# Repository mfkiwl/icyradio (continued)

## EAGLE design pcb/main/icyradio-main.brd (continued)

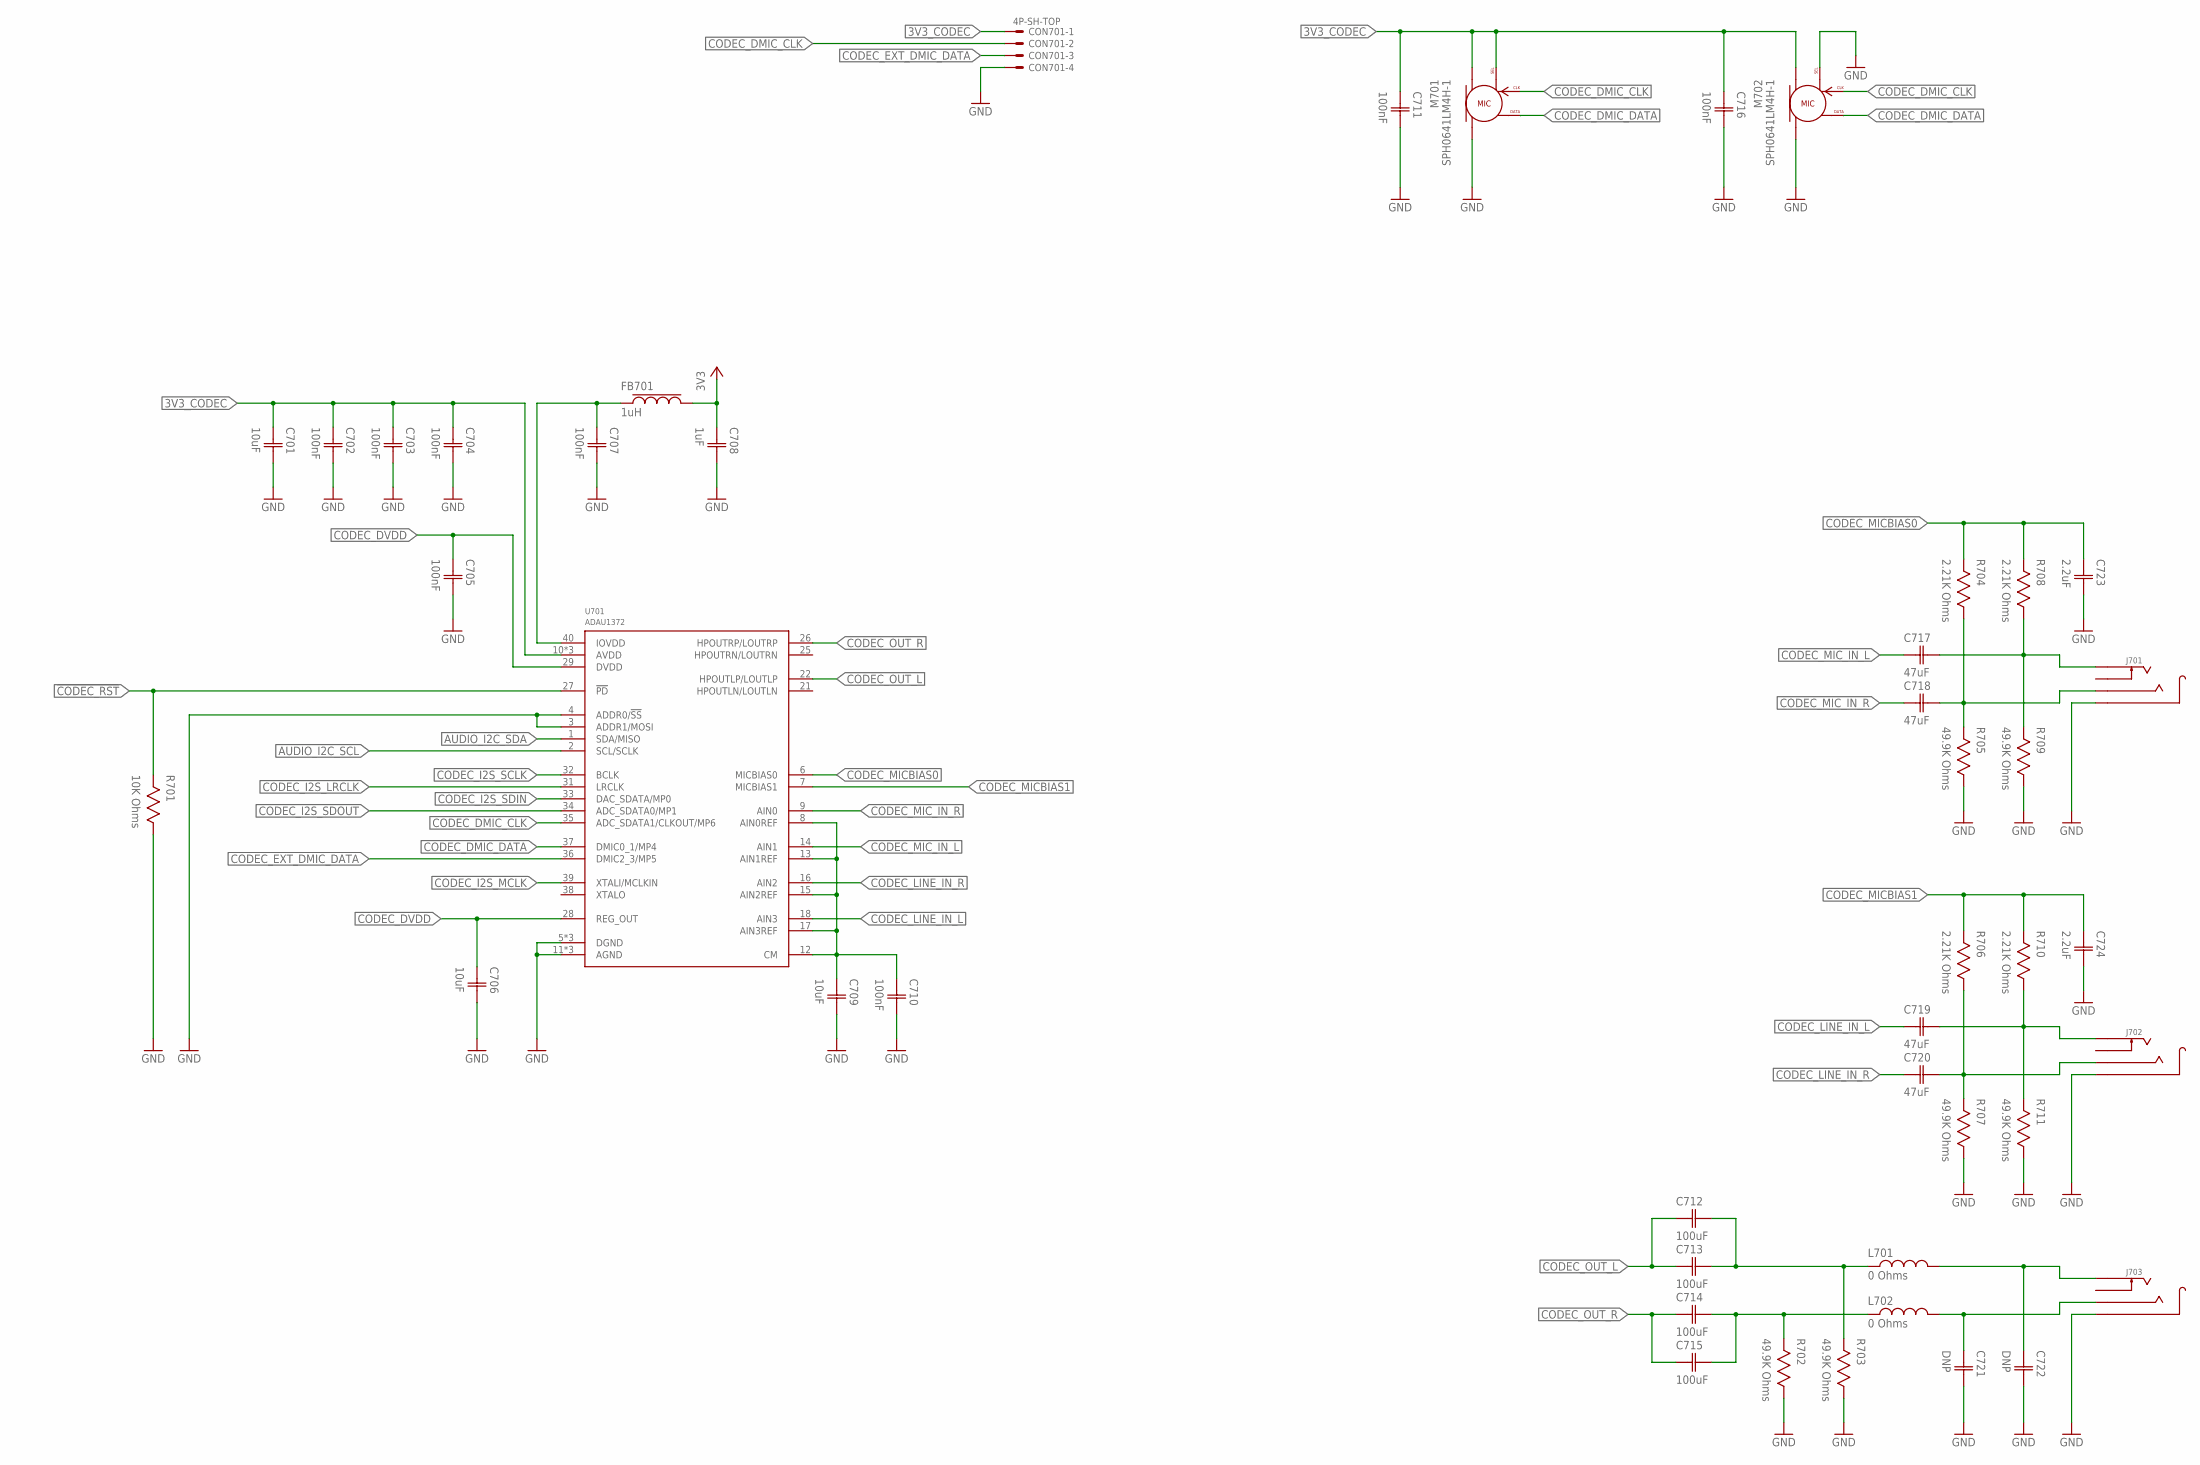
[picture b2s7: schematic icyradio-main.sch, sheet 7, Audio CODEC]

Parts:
C701, C706, C709: 10uF; CAP0402
C702, C703, C704, C705, C707, C710, C711, C716: 100nF; CAP0402
C708: 1uF; CAP0402
C712, C713, C714, C715: 100uF; CAP0805
C717, C718, C719, C720: 47uF; CAP0603
C721, C722: DNP; CAP0402
C723, C724: 2.2uF; CAP0402
CON701: 4P-SH-TOP; SH-04-TOP
FB701: 1uH; IND0603
J701, J702, J703: TRSJACK; 3.5TRSJACK
L701, L702: 0 Ohms; IND0603
M701, M702: SPH0641LM4H-1
R701: 10K Ohms; RES0402
R702, R703, R705, R707, R709, R711: 49.9K Ohms; RES0402
R704, R706, R708, R710: 2.21K Ohms; RES0402
U701: ADAU1372; QFN40

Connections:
3V3: C708.1 (C1), FB701.2; also elsewhere on the board
3V3_CODEC: C701.1 (C1), C702.1 (C1), C703.1 (C1), C704.1 (C1), C711.1 (C1), C716.1 (C1), CON701.1, M701.2 (SEL), M701.5 (VCC), M702.5 (VCC), U701.10 (AVDD), U701.19 (AVDD), U701.24 (AVDD); also elsewhere on the board
3V3_CODEC_DIG: C707.1 (C1), FB701.1, U701.40 (IOVDD)
!CODEC_RST: R701.2, U701.27 (!PD); also elsewhere on the board
AUDIO_I2C_SCL: U701.2 (SCL/SCLK); also elsewhere on the board
AUDIO_I2C_SDA: U701.1 (SDA/MISO); also elsewhere on the board
CODEC_CM: C709.1 (C1), C710.1 (C1), U701.8 (AIN0REF), U701.12 (CM), U701.13 (AIN1REF), U701.15 (AIN2REF), U701.17 (AIN3REF)
CODEC_DMIC_CLK: CON701.2, M701.4 (CLK), M702.4 (CLK), U701.35 (ADC_SDATA1/CLKOUT/MP6)
CODEC_DMIC_DATA: M701.1 (DAT), M702.1 (DAT), U701.37 (DMIC0_1/MP4)
CODEC_DVDD: C705.1 (C1), C706.1 (C1), U701.28 (REG_OUT), U701.29 (DVDD)
CODEC_EXT_DMIC_DATA: CON701.3, U701.36 (DMIC2_3/MP5)
CODEC_I2S_LRCLK: U701.31 (LRCLK); also elsewhere on the board
CODEC_I2S_MCLK: U701.39 (XTALI/MCLKIN); also elsewhere on the board
CODEC_I2S_SCLK: U701.32 (BCLK); also elsewhere on the board
CODEC_I2S_SDIN: U701.33 (DAC_SDATA/MP0); also elsewhere on the board
CODEC_I2S_SDOUT: U701.34 (ADC_SDATA0/MP1); also elsewhere on the board
CODEC_LINE_IN_L: C719.1 (C1), U701.18 (AIN3)
CODEC_LINE_IN_R: C720.1 (C1), U701.16 (AIN2)
CODEC_MICBIAS0: C723.1 (C1), R704.2, R708.2, U701.6 (MICBIAS0)
CODEC_MICBIAS1: C724.1 (C1), R706.2, R710.2, U701.7 (MICBIAS1)
CODEC_MIC_IN_L: C717.1 (C1), U701.14 (AIN1)
CODEC_MIC_IN_R: C718.1 (C1), U701.9 (AIN0)
CODEC_OUT_L: C712.1 (C1), C713.1 (C1), U701.22 (HPOUTLP/LOUTLP)
CODEC_OUT_R: C714.1 (C1), C715.1 (C1), U701.26 (HPOUTRP/LOUTRP)
GND: C701.2 (C2), C702.2 (C2), C703.2 (C2), C704.2 (C2), C705.2 (C2), C706.2 (C2), C707.2 (C2), C708.2 (C2), C709.2 (C2), C710.2 (C2), C711.2 (C2), C716.2 (C2), C721.2 (C2), C722.2 (C2), C723.2 (C2), C724.2 (C2), CON701.4, J701.1 (S), J702.1 (S), J703.1 (S), M701.3 (GND), M702.2 (SEL), M702.3 (GND), R701.1, R702.1, R703.1, R705.1, R707.1, R709.1, R711.1, U701.3 (ADDR1/MOSI), U701.4 (ADDR0/!SS), U701.5 (DGND), U701.11 (AGND), U701.20 (AGND), U701.23 (AGND), U701.30 (DGND), U701.41 (DGND); also elsewhere on the board
unnamed: C720.2 (C2), J702.3 (R), R706.1, R707.2
unnamed: C719.2 (C2), J702.2 (T), R710.1, R711.2
unnamed: C718.2 (C2), J701.3 (R), R704.1, R705.2
unnamed: C717.2 (C2), J701.2 (T), R708.1, R709.2
unnamed: C714.2 (C2), C715.2 (C2), L702.1, R702.2
unnamed: C712.2 (C2), C713.2 (C2), L701.1, R703.2
unnamed: C721.1 (C1), J703.3 (R), L702.2
unnamed: C722.1 (C1), J703.2 (T), L701.2

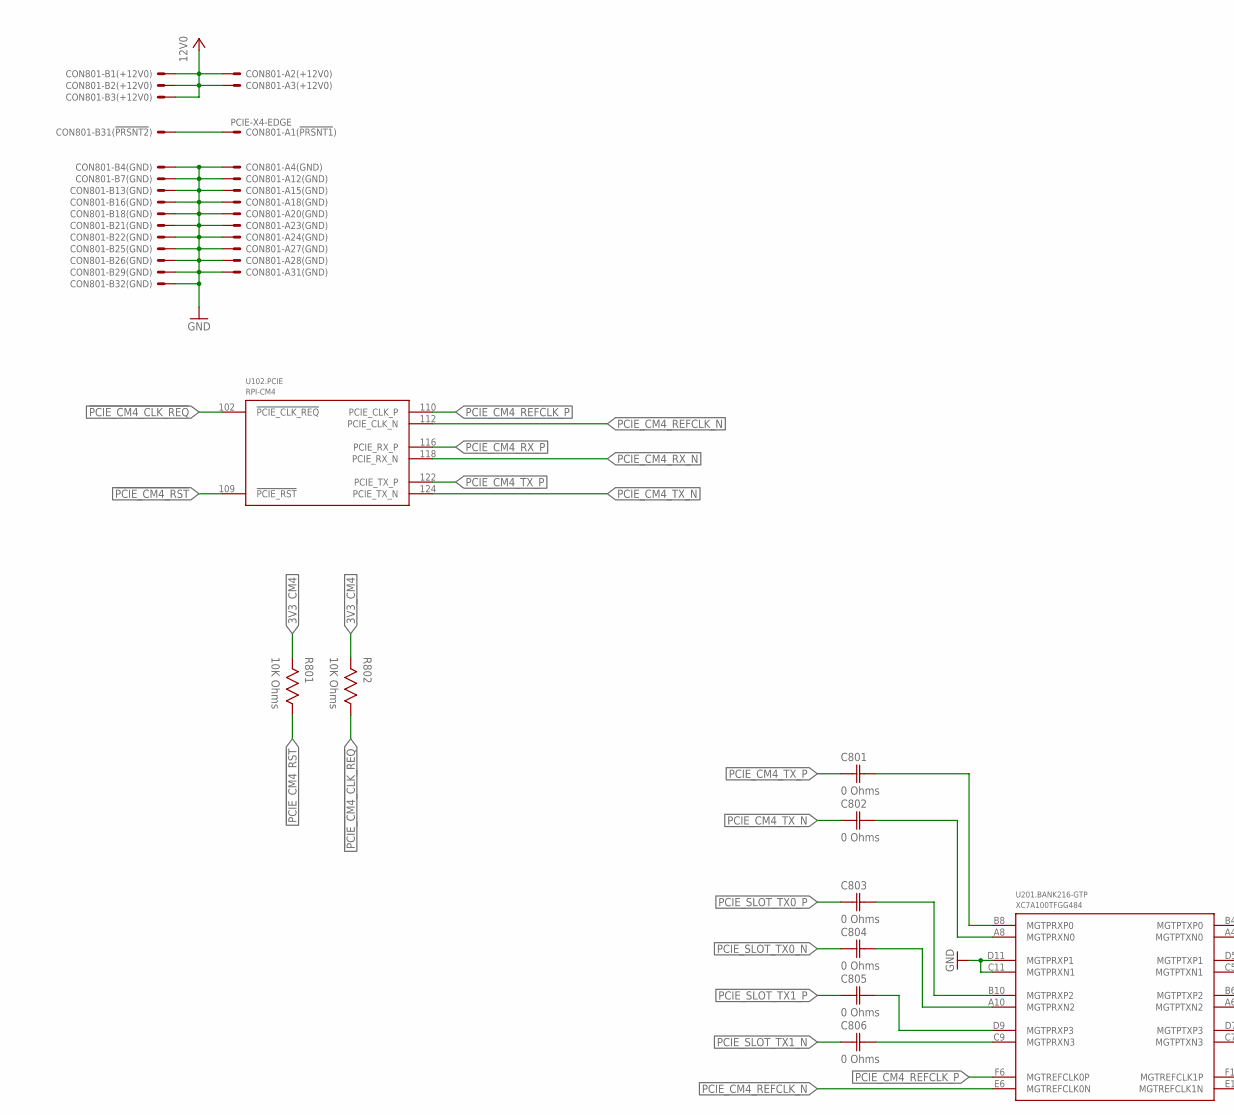
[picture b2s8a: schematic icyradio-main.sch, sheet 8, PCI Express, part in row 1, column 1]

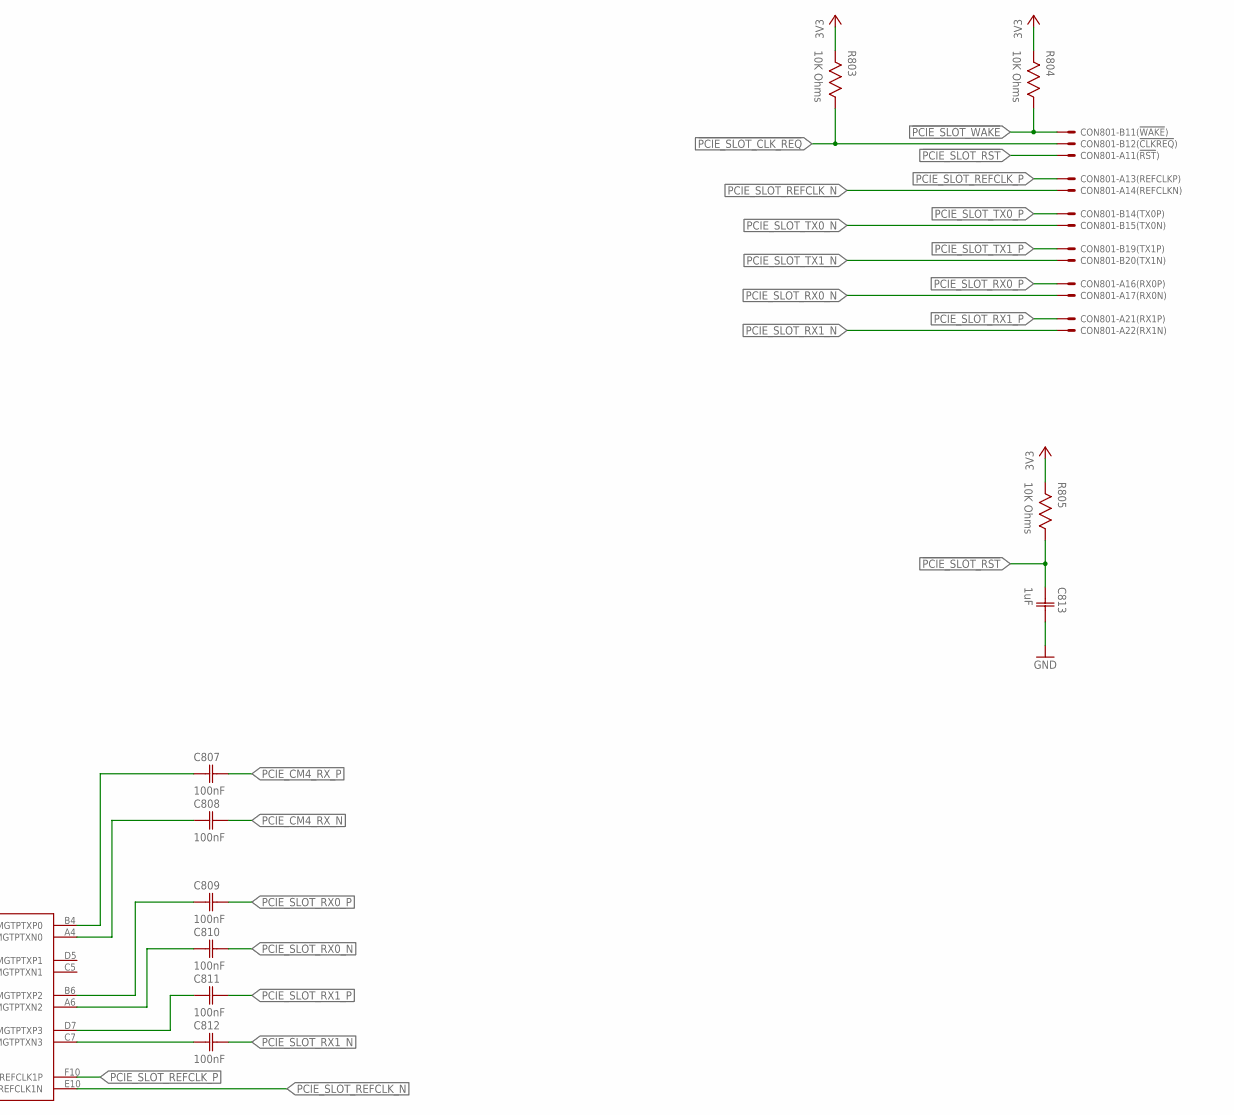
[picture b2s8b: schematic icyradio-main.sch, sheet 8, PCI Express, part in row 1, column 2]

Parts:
C801, C802, C803, C804, C805, C806: 0 Ohms; CAP0402
C807, C808, C809, C810, C811, C812: 100nF; CAP0402
C813: 1uF; CAP0402
CON801: PCIE-X4-EDGE
R801, R802, R803, R804, R805: 10K Ohms; RES0402
U102: RPI-CM4
U201: XC7A100TFGG484; FGG484

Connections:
3V3: R803.2, R804.2, R805.2; also elsewhere on the board
3V3_CM4: R801.2, R802.2; also elsewhere on the board
12V0: CON801.A2, CON801.A3, CON801.B1, CON801.B2, CON801.B3; also elsewhere on the board
!PCIE_CM4_CLK_REQ: R802.1, U102.102 (!PCIE_CLK_REQ); also elsewhere on the board
!PCIE_CM4_RST: R801.1, U102.109 (!PCIE_RST); also elsewhere on the board
!PCIE_SLOT_CLK_REQ: CON801.B12, R803.1; also elsewhere on the board
!PCIE_SLOT_PRSNT: CON801.A1, CON801.B31
!PCIE_SLOT_RST: C813.1 (C1), CON801.A11, R805.1; also elsewhere on the board
!PCIE_SLOT_WAKE: CON801.B11, R804.1; also elsewhere on the board
GND: C813.2 (C2), CON801.A4, CON801.A12, CON801.A15, CON801.A18, CON801.A20, CON801.A23, CON801.A24, CON801.A27, CON801.A28, CON801.A31, CON801.B4, CON801.B7, CON801.B13, CON801.B16, CON801.B18, CON801.B21, CON801.B22, CON801.B25, CON801.B26, CON801.B29, CON801.B32, U201.C11 (MGTPRXN1), U201.D11 (MGTPRXP1); also elsewhere on the board
PCIE_CM4_REFCLK_N: U102.112 (PCIE_CLK_N), U201.E6 (MGTREFCLK0N)
PCIE_CM4_REFCLK_P: U102.110 (PCIE_CLK_P), U201.F6 (MGTREFCLK0P)
PCIE_CM4_RX_ACC_N: C808.1 (C1), U201.A4 (MGTPTXN0)
PCIE_CM4_RX_ACC_P: C807.1 (C1), U201.B4 (MGTPTXP0)
PCIE_CM4_RX_N: C808.2 (C2), U102.118 (PCIE_RX_N)
PCIE_CM4_RX_P: C807.2 (C2), U102.116 (PCIE_RX_P)
PCIE_CM4_TX_ACC_N: C802.2 (C2), U201.A8 (MGTPRXN0)
PCIE_CM4_TX_ACC_P: C801.2 (C2), U201.B8 (MGTPRXP0)
PCIE_CM4_TX_N: C802.1 (C1), U102.124 (PCIE_TX_N)
PCIE_CM4_TX_P: C801.1 (C1), U102.122 (PCIE_TX_P)
PCIE_SLOT_REFCLK_N: CON801.A14, U201.E10 (MGTREFCLK1N)
PCIE_SLOT_REFCLK_P: CON801.A13, U201.F10 (MGTREFCLK1P)
PCIE_SLOT_RX0_ACC_N: C810.1 (C1), U201.A6 (MGTPTXN2)
PCIE_SLOT_RX0_ACC_P: C809.1 (C1), U201.B6 (MGTPTXP2)
PCIE_SLOT_RX0_N: C810.2 (C2), CON801.A17
PCIE_SLOT_RX0_P: C809.2 (C2), CON801.A16
PCIE_SLOT_RX1_ACC_N: C812.1 (C1), U201.C7 (MGTPTXN3)
PCIE_SLOT_RX1_ACC_P: C811.1 (C1), U201.D7 (MGTPTXP3)
PCIE_SLOT_RX1_N: C812.2 (C2), CON801.A22
PCIE_SLOT_RX1_P: C811.2 (C2), CON801.A21
PCIE_SLOT_TX0_ACC_N: C804.2 (C2), U201.A10 (MGTPRXN2)
PCIE_SLOT_TX0_ACC_P: C803.2 (C2), U201.B10 (MGTPRXP2)
PCIE_SLOT_TX0_N: C804.1 (C1), CON801.B15
PCIE_SLOT_TX0_P: C803.1 (C1), CON801.B14
PCIE_SLOT_TX1_ACC_N: C806.2 (C2), U201.C9 (MGTPRXN3)
PCIE_SLOT_TX1_ACC_P: C805.2 (C2), U201.D9 (MGTPRXP3)
PCIE_SLOT_TX1_N: C806.1 (C1), CON801.B20
PCIE_SLOT_TX1_P: C805.1 (C1), CON801.B19

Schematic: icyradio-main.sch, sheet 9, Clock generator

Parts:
C901, C904, C905, C907, C908, C909: 100nF; CAP0402
C902, C903: 1uF; CAP0402
C906: 10pF; CAP0402
FB901: 1uH; IND0603
R901: DNP; RES0402
R902, R906, R907, R909, R910, R911, R913: 0 Ohms; RES0402
R903, R904, R905: 10K Ohms; RES0402
R908, R912: 100nF; RES0402
RFCON901, RFCON902: RFCON-U.FL; U.FL
U901: DSB321SDA; TCXO-3225
U902: SI5351C-B-GM; QFN20

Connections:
3V3: C902.1 (C1), FB901.1, R904.2, R905.2; also elsewhere on the board
3V3_CLK_MNGR: C901.1 (C1), C903.1 (C1), C904.1 (C1), C905.1 (C1), C908.1 (C1), C909.1 (C1), FB901.2, U901.4 (VDD), U902.10 (VDDOB), U902.11 (VDDOA), U902.14 (VDDOD), U902.18 (VDDOC), U902.20 (VDD)
!CLK_MNGR_IRQ: R905.1, U902.3 (!INTR); also elsewhere on the board
!CLK_MNGR_OE: R904.1, U902.7 (!OE); also elsewhere on the board
CLK_MNGR_CLK0: R906.2, U902.13 (CLK0)
CLK_MNGR_CLK1: R910.2, U902.12 (CLK1)
CLK_MNGR_CLK2: R907.2, U902.9 (CLK2)
CLK_MNGR_CLK3: R911.2, U902.8 (CLK3)
CLK_MNGR_CLK4: R908.2, U902.19 (CLK4)
CLK_MNGR_CLK5: R912.2, U902.17 (CLK5)
CLK_MNGR_CLK6: R909.2, U902.16 (CLK6)
CLK_MNGR_CLK7: R913.2, U902.15 (CLK7)
CLK_MNGR_CLKIN: R902.1, U902.6 (CLKIN)
CLK_MNGR_EXT_REF: R901.2, R902.2, RFCON901.P$3 (SIGNAL)
CLK_MNGR_REF_ACC: C907.2 (C2), U902.1 (XA)
CLK_MNGR_REF_DCC: C906.1 (C1), C907.1 (C1), R903.2, U901.3 (CLK)
EXT_CLK_2_3: R909.1; also elsewhere on the board
EXT_CLK_OUT: R913.1, RFCON902.P$3 (SIGNAL)
FPGA_CLK0: R907.1; also elsewhere on the board
FPGA_CLK1: R911.1; also elsewhere on the board
FPGA_CLK2: R906.1; also elsewhere on the board
FPGA_CLK3: R910.1; also elsewhere on the board
GND: C901.2 (C2), C902.2 (C2), C903.2 (C2), C904.2 (C2), C905.2 (C2), C906.2 (C2), C908.2 (C2), C909.2 (C2), R901.1, R903.1, RFCON901.P$1 (GND), RFCON901.P$2 (GND), RFCON902.P$1 (GND), RFCON902.P$2 (GND), U901.1 (GND), U901.2 (GND), U902.21 (GND); also elsewhere on the board
SYNTH_REF_CLK: R912.1; also elsewhere on the board
SYS_I2C_SCL: U902.4 (SCL); also elsewhere on the board
SYS_I2C_SDA: U902.5 (SDA); also elsewhere on the board
TRX_REF_CLK: R908.1; also elsewhere on the board

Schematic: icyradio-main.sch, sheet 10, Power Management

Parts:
C1001, C1005, C1006, C1007, C1008, C1010, C1012: 100nF; CAP0402
C1002, C1004: 220pF; CAP0402; VOLTAGE 50V
C1003, C1009, C1011, C1013, C1014: 1uF; CAP0402
D1001: PGB102ST23; SOT23
D1002: SMAJ20A; DO214AC
D1003: B0530W; SOD-123
D1004: LED0603; 0603
F1001: PTC1206; 1206
L1001: 0603USB-951ML; 0603USB
R1001: 330 Ohms; RES0402
R1002, R1003, R1006, R1009, R1011, R1012, R1014: 10K Ohms; RES0402
R1004, R1007: 4.7K Ohms; RES0402
R1005: 90.9K Ohms; RES0402
R1008: 0 Ohms; RES0402
R1010: 470 Ohms; RES0402
R1013: 1K Ohms; RES0402
S1001: TAC_SWITCHSMD_4.5X4.5; TAC_SW_SMD_4.5X4.5
TC1001: TC2050-IDC
TP8, TP9, TP10, TP12: TESTPOINT-0.7MM; PAD0.7MM
U102: RPI-CM4
U1001: LTC4313-3; DFN8
U1002: UPD301C; VQFN40
U1003: MIC2019; SOT23-6
USB1001: USB-C-16P-SMD-FLAT-SIDE-TYPE-2

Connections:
3V3: C1005.1 (C1), U1001.8 (VCC); also elsewhere on the board
3V3_PM: C1007.1 (C1), C1008.1 (C1), C1010.1 (C1), R1002.2, R1004.2, R1007.2, R1011.2, R1014.2, TC1001.1, U1002.6 (VDD33_REG_IN), U1002.14 (VDD33_ALW_IN), U1002.16 (VDD33_IO_IN), U1002.21 (VDD33_ANA_IN); also elsewhere on the board
5V0: C1012.1 (C1), C1013.1 (C1), U1002.3 (VCONN_IN), U1003.1 (VIN); also elsewhere on the board
12V0_EN: U1002.30 (PA15); also elsewhere on the board
12V0_VSENSE: U1002.17 (PA04); also elsewhere on the board
!CM4_BTLDR: U1002.36 (PA22/GPIO6); also elsewhere on the board
!FPGA_INIT: U1002.11 (PA01); also elsewhere on the board
!PMC_BTN: C1003.1 (C1), R1002.1, S1001.3, S1001.4, U1002.38 (GPIO8)
!PMC_RESET: R1014.1, TC1001.10, U1002.33 (!RESET_COM), U1002.40 (!RESET)
!PM_SPI_CS: TP8.TP, U1002.24 (PA10/!SPI_SS0!)
!PM_SPI_IRQ: TP12.TP, U1002.29 (PA14/!IRQ!)
!VBUS_SRC_FAULT: R1011.1, U1002.27 (GPIO3), U1003.4 (!FAULT)
CM4_GLOBAL_EN: U1002.37 (PA23/GPIO7); also elsewhere on the board
CM4_RUNNING: U1002.35 (PA19/GPIO5); also elsewhere on the board
CM4_USB_OTG: U102.101 (USB_OTG_ID), U1002.1 (PA28)
GND: C1001.2 (C2), C1002.2 (C2), C1003.2 (C2), C1004.2 (C2), C1005.2 (C2), C1006.2 (C2), C1007.2 (C2), C1008.2 (C2), C1009.2 (C2), C1010.2 (C2), C1011.2 (C2), C1012.2 (C2), C1013.2 (C2), C1014.2 (C2), D1001.3 (A), D1002.A, D1004.C, R1001.1, R1003.1, R1006.1, R1009.1, R1010.1, R1012.1, S1001.1, S1001.2, TC1001.3, U1001.4 (GND), U1001.9 (GND), U1002.41 (GND), U1003.2 (GND), USB1001.A1/B12 (GND), USB1001.B1/A12 (GND); also elsewhere on the board
unnamed: C1001.1 (C1), R1001.2, USB1001.SHIELD@0 (SHIELD), USB1001.SHIELD@1 (SHIELD), USB1001.SHIELD@2 (SHIELD), USB1001.SHIELD@3 (SHIELD)
unnamed: D1004.A, R1013.1
unnamed: C1009.1 (C1), U1002.15 (VDD18_CORE_OUT), U1002.28 (VPP18)
unnamed: C1011.1 (C1), U1002.5 (VDD12_CORE_OUT)
unnamed: C1014.1 (C1), D1003.A, U1003.6 (VOUT)
unnamed: R1010.2, U1003.5 (ILIMIT)
PMC_LED: R1013.2, U1002.10 (PA00)
PMC_SWCLK: TC1001.4, U1002.7 (PA30)
PMC_SWDIO: TC1001.2, U1002.8 (PA31)
PMC_SWO: R1012.2, TC1001.6, U1002.34 (PA18/GPO4)
PM_I2C_EN: R1003.2, U1001.1 (ENABLE); also elsewhere on the board
PM_I2C_SCL: R1004.1, U1001.2 (SCLOUT), U1002.32 (PA17); also elsewhere on the board
PM_I2C_SDA: R1007.1, U1001.7 (SDAOUT), U1002.31 (PA16); also elsewhere on the board
PM_SPI_CLK: TP10.TP, U1002.23 (PA09/SPI_CLK)
PM_SPI_MISO: TP9.TP, U1002.22 (PA08/SPI_MISO)
PM_SPI_MOSI: R1008.1, U1002.25 (PA11/SPI_MOSI)
PM_SPI_MOSI_SI: R1008.2, U1002.20 (PA07/SPI_MOSI_SI)
SYS_I2C_SCL: U1001.3 (SCLIN); also elsewhere on the board
SYS_I2C_SDA: U1001.6 (SDAIN); also elsewhere on the board
USB_CC1: C1002.1 (C1), U1002.4 (CC1), USB1001.A5 (CC1)
USB_CC2: C1004.1 (C1), U1002.2 (CC2), USB1001.B5 (CC2)
USB_D_N: L1001.2, U102.103 (USB_DN)
USB_D_P: L1001.3, U102.105 (USB_DP)
USB_D_UNFILT_N: D1001.1 (C1), L1001.1, USB1001.A7 (D-), USB1001.B7 (D-)
USB_D_UNFILT_P: D1001.2 (C2), L1001.4, USB1001.A6 (D+), USB1001.B6 (D+)
USB_VBUS_DET: C1006.1 (C1), R1005.1, R1006.2, U1002.9 (VBUS_DET_IN)
VBUS: D1002.C, D1003.C, F1001.1, R1005.2; also elsewhere on the board
VBUS_SNK_EN: U1002.39 (PA27/GPIO9); also elsewhere on the board
VBUS_SRC_EN: R1009.2, U1002.26 (GPIO2), U1003.3 (EN)
VBUS_UNFUSED: F1001.2, USB1001.A4/B9 (VBUS), USB1001.B4/A9 (VBUS)
VBUS_VSENSE: U1002.12 (PA02); also elsewhere on the board
VEXT_EN: U1002.19 (PA06); also elsewhere on the board
VEXT_VSENSE: U1002.18 (PA05); also elsewhere on the board
VIN_VSENSE: U1002.13 (PA03); also elsewhere on the board

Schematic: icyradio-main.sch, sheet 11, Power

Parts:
C1101, C1102, C1106, C1107, C1109, C1113, C1120, C1121, C1129, C1130: 100nF; CAP0402
C1103, C1105, C1110, C1111, C1112: 10uF; CAP1206; VOLTAGE 50V
C1104: 1uF; CAP0603; VOLTAGE 50V
C1108, C1115, C1128: 4.7uF; CAP0402
C1114, C1126: 10uF; CAP0402
C1116, C1117, C1118, C1119: 4.7uF; CAP0603; VOLTAGE 35V
C1122, C1123, C1124, C1125: 100uF; CAP1206
C1127: 4.7uF; CAP0603
CON1101: 2EDG-2P-5MM-H
D1101, D1102, D1103: B0530W; SOD-123
D1104: LED0603; 0603
D1105: SMAJ20A; DO214AC
F1101: 2.6A Hold; 1206
JP1101: PINHD-2X3/SMD; 2X03/SMD
L1101: 4.7uH; XGL6030
L1102: 2.2uH; XGL6030
Q1101, Q1103, Q1106: AO3400; SOT23
Q1102, Q1104, Q1105: AO4805; SOIC8
R1101, R1103, R1108, R1110: 100K Ohms; RES0402
R1102, R1104, R1109, R1111: 5.1K Ohms; RES0402
R1105, R1112, R1115, R1118, R1121, R1122, R1124: 10K Ohms; RES0402
R1106, R1107, R1113, R1114, R1116, R1117, R1119: 1K Ohms; RES0402
R1120, R1123: DNP; RES0402
R1125: 36.5K Ohms; RES0402
R1126: 124K Ohms; RES0402
R1127: 51.1K Ohms; RES0402
R1128: 0 Ohms; RES0402
TP1, TP2, TP3, TP4, TP5, TP6, TP7: TESTPOINT-0.7MM; PAD0.7MM
U1101: MCP1804-3302; SOT23-5
U1102: LT7182S; LQFN40_ASYM_CORNER

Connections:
1V0: C1123.1 (C1), C1125.1 (C1), C1128.1 (C1), C1130.1 (C1), L1102.2, U1102.11 (VSENSEP); also elsewhere on the board
1V0_BOOST: C1121.2 (C2), U1102.13 (BOOST)
1V0_PGOOD: R1122.1, TP2.TP, U1102.32 (PGOOD); also elsewhere on the board
1V0_SW: C1121.1 (C1), L1102.1, U1102.16 (SW), U1102.17 (SW), U1102.44 (SW)
1V2_PGOOD: TP3.TP; also elsewhere on the board
1V8_PGOOD: TP4.TP; also elsewhere on the board
1V8_VIN_REG_VDD: C1115.1 (C1), U1102.7 (VDD18)
1V35_PGOOD: TP7.TP; also elsewhere on the board
2V5: JP1101.6; also elsewhere on the board
2V5_PGOOD: TP5.TP; also elsewhere on the board
3V0_VIN_REG_INTVCC: C1114.1 (C1), U1102.4 (ITH), U1102.5 (ITH), U1102.6 (INTVCC)
3V3: JP1101.5, R1118.2; also elsewhere on the board
3V3_PGOOD: TP6.TP; also elsewhere on the board
3V3_PM: C1108.1 (C1), C1109.1 (C1), C1113.1 (C1), U1101.5 (VOUT), U1102.21 (EXTVCC); also elsewhere on the board
3V5_VIN_REG_DRVCC: C1126.1 (C1), R1120.2, R1123.2, R1124.2, U1102.20 (DRVCC), U1102.27 (!FAULT), U1102.28 (!FAULT)
5V0: C1122.1 (C1), C1124.1 (C1), C1127.1 (C1), C1129.1 (C1), JP1101.1, JP1101.2, L1101.2, R1119.2, R1121.2, R1122.2, U1102.2 (VSENSEP); also elsewhere on the board
5V0_BOOST: C1120.2 (C2), U1102.40 (BOOST)
5V0_PGOOD: R1121.1, TP1.TP, U1102.23 (RUN), U1102.33 (PGOOD); also elsewhere on the board
5V0_SW: C1120.1 (C1), L1101.1, U1102.36 (SW), U1102.37 (SW), U1102.41 (SW)
12V0: C1105.1 (C1), D1102.A, Q1104.5 (D), Q1104.6 (D), R1108.2; also elsewhere on the board
12V0_EN: Q1103.1 (G), R1112.2; also elsewhere on the board
12V0_VSENSE: C1106.1 (C1), R1108.1, R1109.2; also elsewhere on the board
!VIN_REG_ALERT: R1118.1, U1102.29 (!ALERT); also elsewhere on the board
GND: C1101.2 (C2), C1102.2 (C2), C1103.2 (C2), C1104.2 (C2), C1105.2 (C2), C1106.2 (C2), C1107.2 (C2), C1108.2 (C2), C1109.2 (C2), C1110.2 (C2), C1111.2 (C2), C1112.2 (C2), C1113.2 (C2), C1114.2 (C2), C1115.2 (C2), C1116.2 (C2), C1117.2 (C2), C1118.2 (C2), C1119.2 (C2), C1122.2 (C2), C1123.2 (C2), C1124.2 (C2), C1125.2 (C2), C1126.2 (C2), C1127.2 (C2), C1128.2 (C2), C1129.2 (C2), C1130.2 (C2), CON1101.P$1, D1104.C, D1105.A, JP1101.3, JP1101.4, Q1101.2 (S), Q1103.2 (S), Q1106.2 (S), R1102.1, R1104.1, R1105.1, R1109.1, R1111.1, R1112.1, R1115.1, R1125.1, R1126.1, R1127.1, R1128.1, U1101.2 (GND), U1102.1 (VSENSEN), U1102.3 (SGND), U1102.12 (VSENSEN), U1102.14 (PGND), U1102.19 (PGND), U1102.34 (PGND), U1102.39 (PGND), U1102.42 (PGND), U1102.43 (PGND), U1102.45 (PGND), U1102.46 (PGND), U1102.47 (PGND), U1102.48 (PGND); also elsewhere on the board
unnamed: Q1102.1 (S), Q1102.3 (S), R1106.2
unnamed: Q1102.2 (G), Q1102.4 (G), R1106.1, R1107.2
unnamed: Q1101.3 (D), R1107.1
unnamed: Q1104.1 (S), Q1104.3 (S), R1113.2
unnamed: Q1104.2 (G), Q1104.4 (G), R1113.1, R1114.2
unnamed: Q1103.3 (D), R1114.1
unnamed: Q1105.1 (S), Q1105.3 (S), R1116.2
unnamed: Q1105.2 (G), Q1105.4 (G), R1116.1, R1117.2
unnamed: Q1106.3 (D), R1117.1
unnamed: D1104.A, R1119.1
PM_I2C_SCL: U1102.30 (SCL); also elsewhere on the board
PM_I2C_SDA: U1102.31 (SDA); also elsewhere on the board
VBUS: C1103.1 (C1), D1101.A, Q1102.5 (D), Q1102.6 (D), R1110.2; also elsewhere on the board
VBUS_SNK_EN: Q1101.1 (G), R1105.2; also elsewhere on the board
VBUS_VSENSE: C1107.1 (C1), R1110.1, R1111.2; also elsewhere on the board
VEXT: C1110.1 (C1), D1103.A, D1105.C, F1101.1, Q1105.7 (D), Q1105.8 (D), R1103.2
VEXT_EN: Q1106.1 (G), R1115.2; also elsewhere on the board
VEXT_UNFUSED: CON1101.P$2, F1101.2
VEXT_VSENSE: C1102.1 (C1), R1103.1, R1104.2; also elsewhere on the board
VIN: C1111.1 (C1), C1112.1 (C1), C1116.1 (C1), C1117.1 (C1), C1118.1 (C1), C1119.1 (C1), Q1102.7 (D), Q1102.8 (D), Q1104.7 (D), Q1104.8 (D), Q1105.5 (D), Q1105.6 (D), R1101.2, U1102.15 (PVIN), U1102.18 (PVIN), U1102.35 (PVIN), U1102.38 (PVIN)
VIN_PM: C1104.1 (C1), D1101.C, D1102.C, D1103.C, U1101.1 (VIN), U1101.4 (!SHDN)
VIN_REG_ASEL: R1128.2, U1102.10 (ASEL)
VIN_REG_PWM_CFG: R1127.2, U1102.22 (SYNC/PWM_CFG)
VIN_REG_RUN0: R1123.1, U1102.24 (RUN)
VIN_REG_SHARE_CLK: R1124.1, U1102.25 (SHARE_CLK)
VIN_REG_VOUT0_CFG: R1126.2, U1102.8 (VOUT0_CFG)
VIN_REG_VOUT1_CFG: R1125.2, U1102.9 (VOUT1_CFG/POLYPHASE_CFG)
VIN_REG_WP: R1120.1, U1102.26 (WP)
VIN_VSENSE: C1101.1 (C1), R1101.1, R1102.2; also elsewhere on the board

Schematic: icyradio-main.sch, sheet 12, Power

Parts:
C1201, C1202, C1203, C1204, C1209, C1215, C1226, C1228, C1229, C1230, C1239, C1245, C1247, C1250, C1253, C1256: 100nF; CAP0402
C1205, C1232, C1242, C1248, C1258: 4.7uF; CAP0603
C1206, C1207, C1208, C1231, C1233: 10nF; CAP0402
C1210, C1227, C1246, C1254: 100uF; CAP1206
C1211, C1221, C1249, C1251, C1252: 470pF; CAP0402
C1212: 10uF; CAP0603
C1213, C1214, C1216, C1217, C1218, C1219, C1220, C1235, C1236, C1237, C1238, C1240, C1241, C1243, C1244, C1255, C1257, C1259: 10uF; CAP0402
C1222, C1223: 47uF; CAP0603
C1224: 4.7uF; CAP0402
C1225, C1234: 1uF; CAP0402
L1201, L1202, L1203, L1205: 2.2uH; XGL35XX
L1204: 4.7uH; XGL35XX
R1201, R1204, R1207, R1210, R1211: 10K Ohms; RES0402
R1202: 118K Ohms; RES0402
R1203: 100K Ohms; RES0402
R1205: 301K Ohms; RES0402
R1206: 158K Ohms; RES0402
R1208: 324K Ohms; RES0402
R1209: 107K Ohms; RES0402
R1212: 309K Ohms; RES0402
R1213: 71.5K Ohms; RES0402
R1214: 274K Ohms; RES0402
R1215: 294K Ohms; RES0402
U1201: ADM7172ACPZ-5.0; LFCSP8_3X3
U1202, U1206: ADM7171ACPZ-1.3; LFCSP8_3X3
U1203, U1207: ADM7171ACPZ-3.3; LFCSP8_3X3
U1204, U1208: MIC23159; VQFN20
U1205: MIC5166; DFN10
U1209: MIC23155; DFN10_0.65P
U1210: ADP7142AUJZ-3.3; SOT23-5

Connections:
0V675_DDR3_VREF: C1234.1 (C1), U1205.1 (VREF); also elsewhere on the board
0V675_DDR3_VTT: C1235.1 (C1), C1238.1 (C1), U1205.6 (SNS), U1205.9 (VTT); also elsewhere on the board
1V0_PGOOD: U1209.2 (EN); also elsewhere on the board
1V2: C1257.1 (C1), C1259.1 (C1), L1205.2, R1214.2, U1209.3 (SNS); also elsewhere on the board
1V2_FB: R1214.1, R1215.2, U1209.4 (FB)
1V2_PGOOD: R1210.1, U1204.9 (EN), U1208.9 (EN), U1208.18 (EN), U1209.5 (PG); also elsewhere on the board
1V2_SS: C1251.1 (C1), U1209.6 (SS)
1V2_SW: L1205.1, U1209.1 (SW)
1V3_TRX: C1236.1 (C1), C1240.1 (C1), C1243.1 (C1), C1244.1 (C1), U1206.1 (VOUT), U1206.2 (VOUT), U1206.3 (SENSE); also elsewhere on the board
1V3_TRX_LO_SYNTH: C1213.1 (C1), C1216.1 (C1), C1218.1 (C1), C1219.1 (C1), U1202.1 (VOUT), U1202.2 (VOUT), U1202.3 (SENSE); also elsewhere on the board
1V8: C1226.1 (C1), C1227.1 (C1), L1202.2, R1204.2, R1205.2, U1204.10 (SNS); also elsewhere on the board
1V8_FB: R1205.1, R1206.2, U1204.11 (FB)
1V8_PGOOD: R1204.1, U1204.12 (PG), U1204.18 (EN); also elsewhere on the board
1V8_SS: C1221.1 (C1), U1204.13 (SS)
1V8_SW: L1202.1, U1204.4 (SW)
1V35: C1209.1 (C1), C1210.1 (C1), C1220.1 (C1), C1224.1 (C1), L1201.1, R1201.2, R1202.2, U1204.17 (SNS), U1205.4 (VDDQ), U1205.10 (VIN); also elsewhere on the board
1V35_FB: R1202.1, R1203.2, U1204.16 (FB)
1V35_PGOOD: R1201.1, U1204.15 (PG), U1205.7 (EN); also elsewhere on the board
1V35_SS: C1211.1 (C1), U1204.14 (SS)
1V35_SW: L1201.2, U1204.3 (SW)
2V5: C1203.1 (C1), C1222.1 (C1), C1228.1 (C1), C1245.1 (C1), C1246.1 (C1), L1203.1, R1207.2, R1208.2, U1202.7 (VIN), U1202.8 (VIN), U1206.7 (VIN), U1206.8 (VIN), U1208.17 (SNS); also elsewhere on the board
2V5_FB: R1208.1, R1209.2, U1208.16 (FB)
2V5_PGOOD: R1207.1, U1202.5 (EN), U1206.5 (EN), U1208.15 (PG); also elsewhere on the board
2V5_SS: C1249.1 (C1), U1208.14 (SS)
2V5_SW: L1203.2, U1208.3 (SW)
3V3: C1253.1 (C1), C1254.1 (C1), L1204.2, R1211.2, R1212.2, U1208.10 (SNS); also elsewhere on the board
3V3_CODEC: C1255.1 (C1), U1210.4 (SENSE/ADJ), U1210.5 (VOUT); also elsewhere on the board
3V3_FB: R1212.1, R1213.2, U1208.11 (FB)
3V3_PGOOD: R1211.1, U1208.12 (PG); also elsewhere on the board
3V3_SS: C1252.1 (C1), U1208.13 (SS)
3V3_SW: L1204.1, U1208.4 (SW)
3V3_SYNTH_IN_PD_FB: C1214.1 (C1), C1217.1 (C1), U1203.1 (VOUT), U1203.2 (VOUT), U1203.3 (SENSE); also elsewhere on the board
3V3_SYNTH_VCO_RF: C1237.1 (C1), C1241.1 (C1), U1207.1 (VOUT), U1207.2 (VOUT), U1207.3 (SENSE); also elsewhere on the board
5V0: C1201.1 (C1), C1202.1 (C1), C1204.1 (C1), C1205.1 (C1), C1223.1 (C1), C1225.1 (C1), C1229.1 (C1), C1230.1 (C1), C1232.1 (C1), C1239.1 (C1), C1242.1 (C1), C1247.1 (C1), C1248.1 (C1), C1250.1 (C1), C1256.1 (C1), C1258.1 (C1), R1210.2, U1201.7 (VIN), U1201.8 (VIN), U1203.7 (VIN), U1203.8 (VIN), U1204.1 (VIN), U1204.6 (VIN), U1204.7 (AVIN), U1204.20 (AVIN), U1205.2 (BIAS), U1207.7 (VIN), U1207.8 (VIN), U1208.1 (VIN), U1208.6 (VIN), U1208.7 (AVIN), U1208.20 (AVIN), U1209.8 (VIN), U1209.9 (VIN), U1210.1 (VIN); also elsewhere on the board
5V0_PGOOD: U1201.5 (EN), U1203.5 (EN), U1207.5 (EN), U1210.3 (EN); also elsewhere on the board
5V0_TRX_RF: C1212.1 (C1), C1215.1 (C1), U1201.1 (VOUT), U1201.2 (VOUT), U1201.3 (SENSE); also elsewhere on the board
GND: C1201.2 (C2), C1202.2 (C2), C1203.2 (C2), C1204.2 (C2), C1205.2 (C2), C1206.2 (C2), C1207.2 (C2), C1208.2 (C2), C1209.2 (C2), C1210.2 (C2), C1211.2 (C2), C1212.2 (C2), C1213.2 (C2), C1214.2 (C2), C1215.2 (C2), C1216.2 (C2), C1217.2 (C2), C1218.2 (C2), C1219.2 (C2), C1220.2 (C2), C1221.2 (C2), C1222.2 (C2), C1223.2 (C2), C1224.2 (C2), C1225.2 (C2), C1226.2 (C2), C1227.2 (C2), C1228.2 (C2), C1229.2 (C2), C1230.2 (C2), C1231.2 (C2), C1232.2 (C2), C1233.2 (C2), C1234.2 (C2), C1235.2 (C2), C1236.2 (C2), C1237.2 (C2), C1238.2 (C2), C1239.2 (C2), C1240.2 (C2), C1241.2 (C2), C1242.2 (C2), C1243.2 (C2), C1244.2 (C2), C1245.2 (C2), C1246.2 (C2), C1247.2 (C2), C1248.2 (C2), C1249.2 (C2), C1250.2 (C2), C1251.2 (C2), C1252.2 (C2), C1253.2 (C2), C1254.2 (C2), C1255.2 (C2), C1256.2 (C2), C1257.2 (C2), C1258.2 (C2), C1259.2 (C2), R1203.1, R1206.1, R1209.1, R1213.1, R1215.1, U1201.6 (GND), U1201.9 (GND), U1202.6 (GND), U1202.9 (GND), U1203.6 (GND), U1203.9 (GND), U1204.2 (PGND), U1204.5 (PGND), U1204.8 (AGND), U1204.19 (AGND), U1204.21 (PGND), U1205.3 (AGND), U1205.8 (PGND), U1205.11 (AGND), U1206.6 (GND), U1206.9 (GND), U1207.6 (GND), U1207.9 (GND), U1208.2 (PGND), U1208.5 (PGND), U1208.8 (AGND), U1208.19 (AGND), U1208.21 (PGND), U1209.7 (AGND), U1209.10 (PGND), U1209.11 (PGND), U1210.2 (GND); also elsewhere on the board
unnamed: C1207.1 (C1), U1202.4 (SS)
unnamed: C1206.1 (C1), U1201.4 (SS)
unnamed: C1231.1 (C1), U1206.4 (SS)
unnamed: C1208.1 (C1), U1203.4 (SS)
unnamed: C1233.1 (C1), U1207.4 (SS)

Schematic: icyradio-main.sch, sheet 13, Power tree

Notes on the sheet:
LT7182S 5.2V @ 6A
ADP150/ADP7142 3.3V @ 150mA
Analog Rail Audio CODEC
ADM7172 5.0V @ 2A
Analog Rail TX RF Amplifiers, RX RF Bias Ts
Digital Rail Compute Module 4
MIC23159 3.3V @ 2A
MIC23159 2.5V @ 2A
Digital Rail FPGA IO Banks 0/13/14, Misc
MIC23155 1.2V @ 2A
Digital Rail FPGA GTP VTT
Digital Rail FPGA IO Banks 34/35, DDR3 VDDQ
Digital Rail FPGA Auxiliary
MIC23159 1.35V @ 2A
MIC23159 1.8V @ 2A
MIC5166 0.675V @ 10mA 0.675V @ 3A
Digital Rail DDR3 VREF
Digital Rail DDR3 VTT
Power Sequence
1.0V
1.2V
1.35V
1.8V
1.3V
5.2V
LT7182S 1.0V @ 6A
Digital Rail FPGA Core, FPGA GTP VCC
3.3V
2.5V
0.675V
MCP1804 3.3V @ 150mA
Digital Rail Power Management & TCPC MCU
VEXT 9 to 20V
PCI Express slot 12V @ 2.1A*
USB VBUS 9 to 20V
ADM7171 1.3V @ 1A
Analog Rail AD9361 LOs and Synthesizers
Analog Rail AD9361 Baseband, Core, TX bias
Digital Rail FPGA Banks 15/16, AD9361 Interface
Analog Rail mmWave Synth VDDPDCP, VDDFB, VDDIN

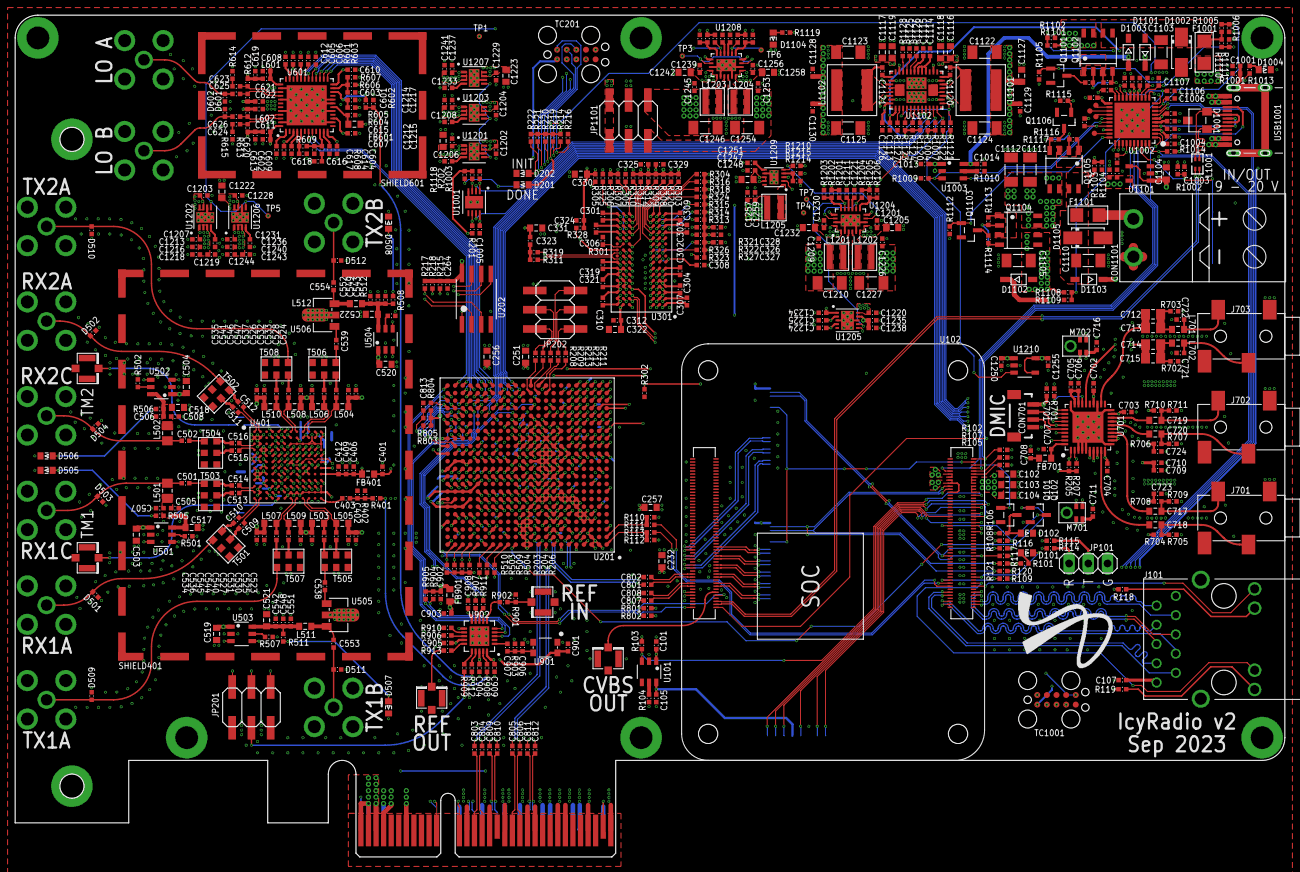
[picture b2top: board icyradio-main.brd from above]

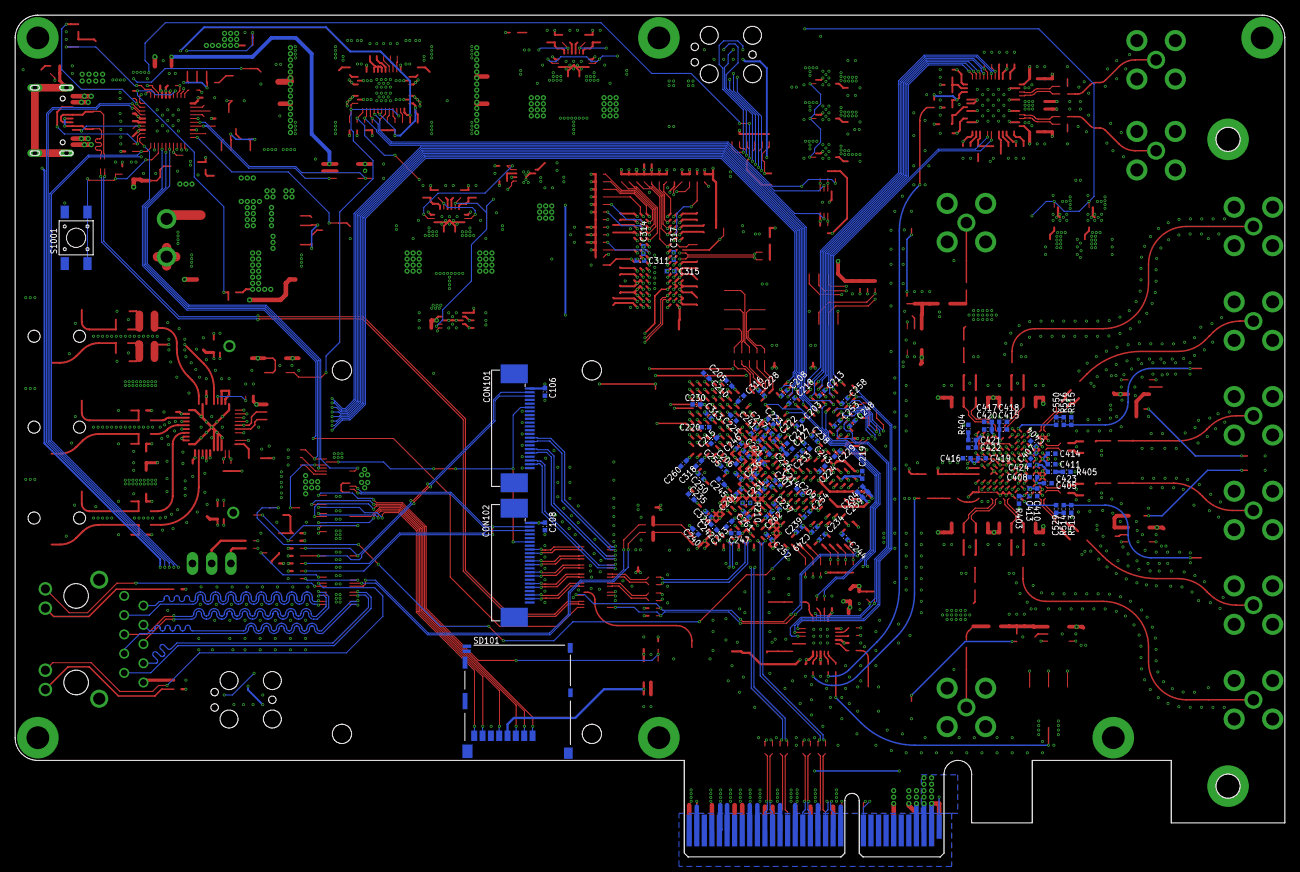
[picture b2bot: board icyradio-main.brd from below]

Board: 6 copper layers, 167.7 x 111.2 mm, 702 parts (101 on the bottom side), 512 nets.
